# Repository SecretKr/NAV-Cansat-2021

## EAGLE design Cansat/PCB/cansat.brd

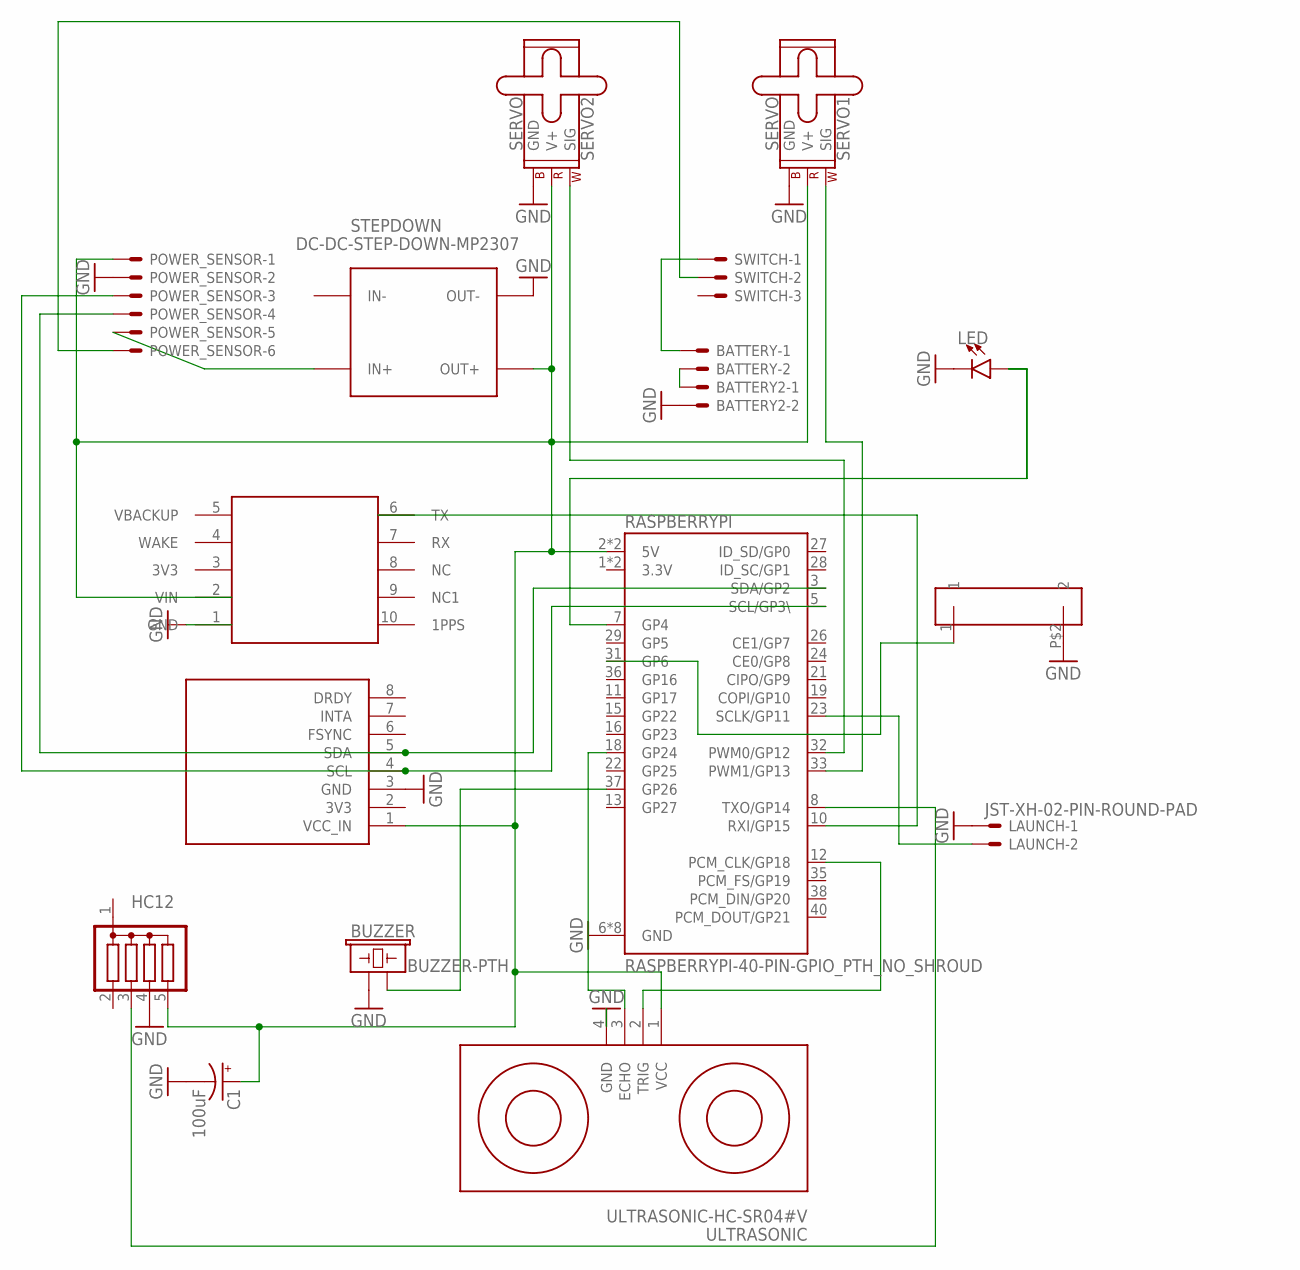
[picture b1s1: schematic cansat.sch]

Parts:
BATTERY, BATTERY2: JST-XH-02-PIN-ROUND-PAD; JST-XH-02-PACKAGE-ROUND-PAD
BUZZER: BUZZER-PTH; BUZZER-12MM
C1: 100uF; CPOL-RADIAL-2.5MM-6.5MM
GPS: AIR530; AIR530FOOTPRINT
HC12: G04R; SIL5
LAUNCH: JST-XH-02-PIN-ROUND-PAD; JST-XH-02-PACKAGE-ROUND-PAD
LED: LED5MM; LED_5MM
MPU: GY-86
POWER_SENSOR: JST-XH-06-PIN-ROUND-PAD; JST-XH-06-PACKAGE-ROUND-PAD
RASPBERRYPI: RASPBERRYPI-40-PIN-GPIO_PTH_NO_SHROUD; 2X20
SENSOR: PENCIL
SERVO1, SERVO2: SERVO; 1X03
STEPDOWN: DC-DC-STEP-DOWN-MP2307
SWITCH: JST-XH-03-PIN-ROUND-PAD; JST-XH-03-PACKAGE-ROUND-PAD
ULTRASONIC: ULTRASONIC-HC-SR04#V

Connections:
3.3V: RASPBERRYPI.1 (3.3V), RASPBERRYPI.17 (3.3V)
GND: BATTERY2.2, BUZZER.+ (1), C1.2 (-), GPS.1 (GND), HC12.4, LAUNCH.1, LED.K (C), MPU.3 (GND), POWER_SENSOR.2, RASPBERRYPI.6 (GND), RASPBERRYPI.9 (GND), RASPBERRYPI.14 (GND), RASPBERRYPI.20 (GND), RASPBERRYPI.25 (GND), RASPBERRYPI.30 (GND), RASPBERRYPI.34 (GND), RASPBERRYPI.39 (GND), SENSOR.P$2 (2), SERVO1.3 (GND), SERVO2.3 (GND), STEPDOWN.OUT-, ULTRASONIC.4 (GND)
unnamed: C1.1 (+), GPS.2 (VIN), HC12.5, MPU.1 (VCC_IN), POWER_SENSOR.1, RASPBERRYPI.2 (5V), RASPBERRYPI.4 (5V), SERVO1.2 (V+), SERVO2.2 (V+), STEPDOWN.OUT+, ULTRASONIC.1 (VCC)
unnamed: LED.A, RASPBERRYPI.7 (GP4)
unnamed: BATTERY.2, BATTERY2.1
unnamed: BATTERY.1, SWITCH.1
unnamed: POWER_SENSOR.6, SWITCH.2
unnamed: GPS.6 (TX), RASPBERRYPI.10 (RXI/GP15)
unnamed: HC12.3, RASPBERRYPI.8 (TXO/GP14)
unnamed: MPU.5 (SDA), POWER_SENSOR.4, RASPBERRYPI.3 (SDA/GP2)
unnamed: MPU.4 (SCL), POWER_SENSOR.3, RASPBERRYPI.5 (SCL/GP3\)
unnamed: RASPBERRYPI.12 (PCM_CLK/GP18), ULTRASONIC.2 (TRIG)
unnamed: RASPBERRYPI.18 (GP24), ULTRASONIC.3 (ECHO)
unnamed: RASPBERRYPI.32 (PWM0/GP12), SERVO2.1 (SIG)
unnamed: RASPBERRYPI.33 (PWM1/GP13), SERVO1.1 (SIG)
unnamed: BUZZER.- (2), RASPBERRYPI.37 (GP26)
unnamed: LAUNCH.2, RASPBERRYPI.23 (SCLK/GP11)
unnamed: POWER_SENSOR.5, STEPDOWN.IN+
unnamed: RASPBERRYPI.31 (GP6), SENSOR.1

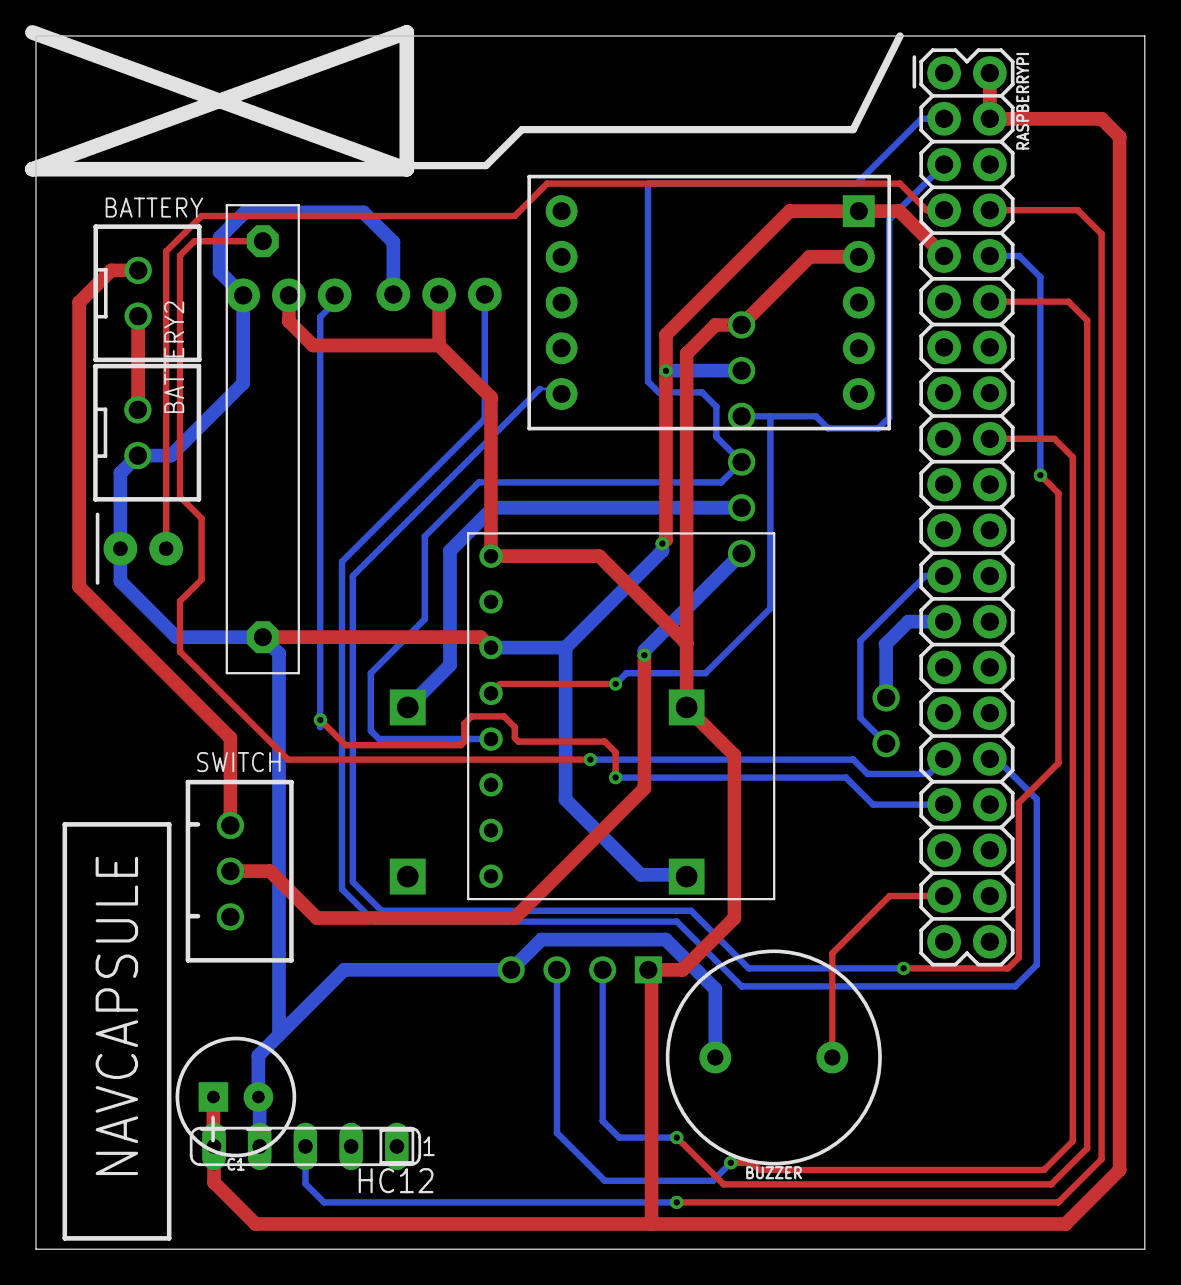
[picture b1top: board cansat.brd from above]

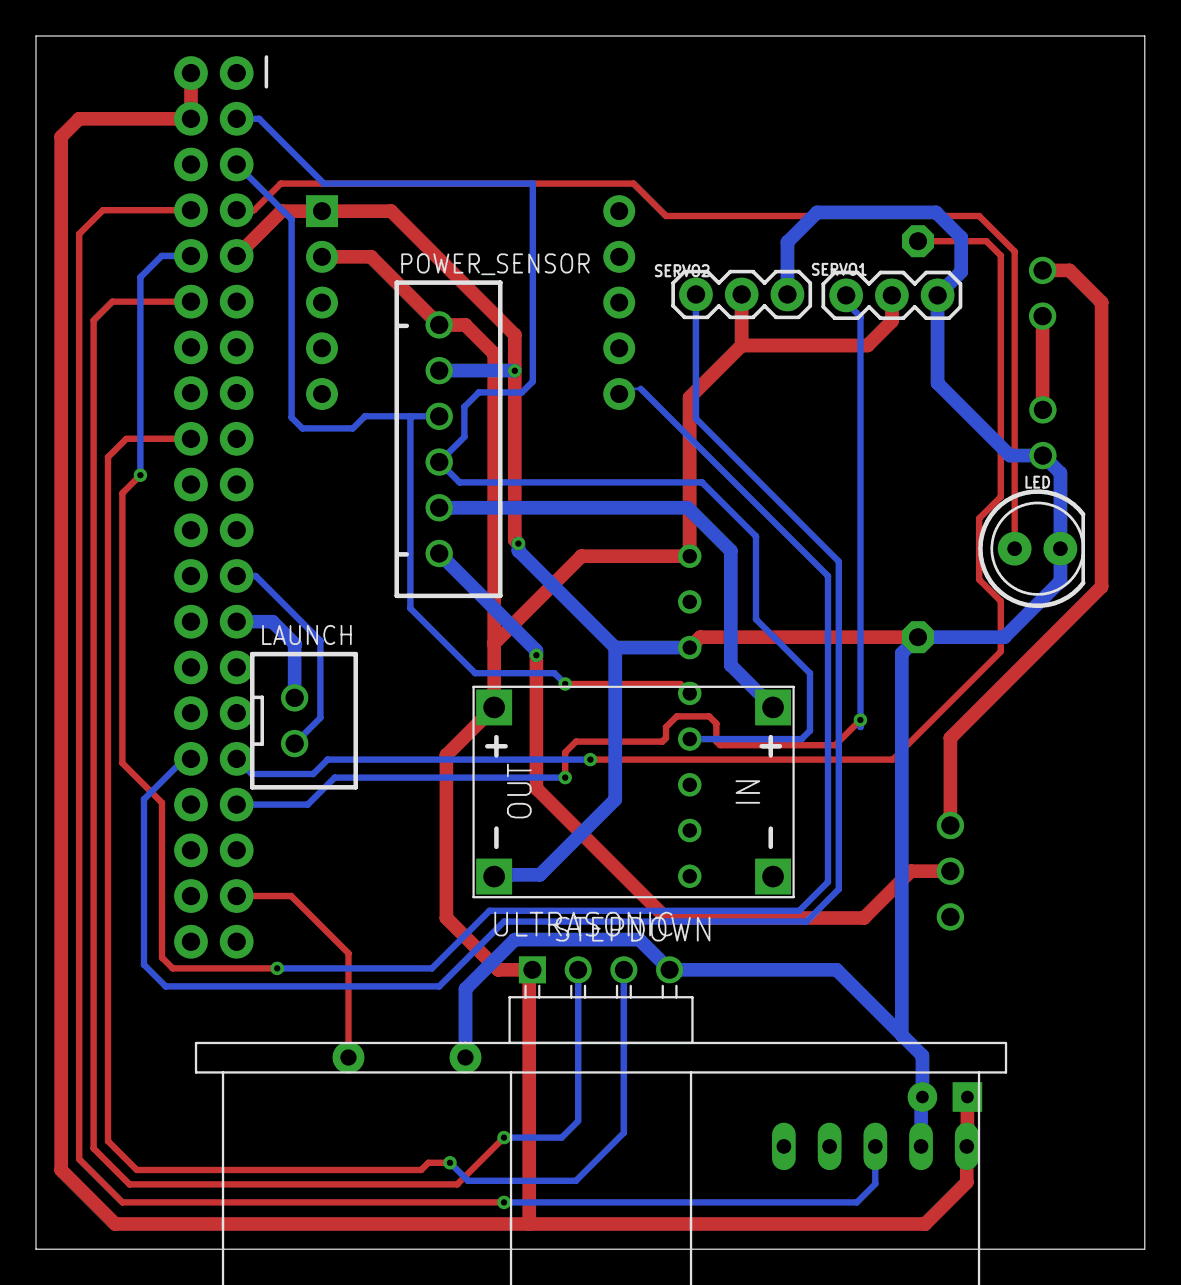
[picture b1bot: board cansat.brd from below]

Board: 2 copper layers, 61.6 x 67.4 mm, 17 parts (7 on the bottom side), 19 nets.

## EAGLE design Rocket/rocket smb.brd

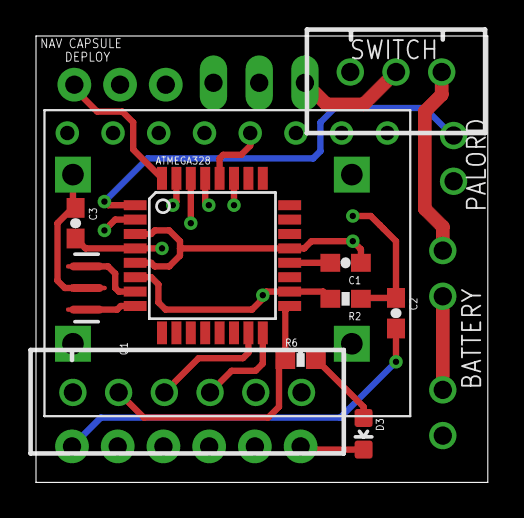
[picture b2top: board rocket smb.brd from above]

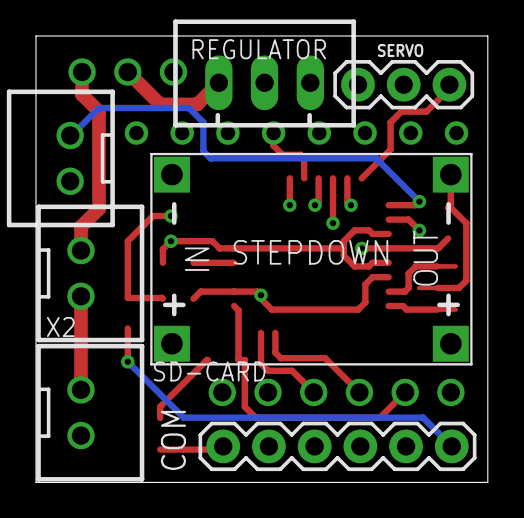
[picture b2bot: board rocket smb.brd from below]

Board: 4 copper layers, 25.1 x 24.8 mm, 18 parts (7 on the bottom side), 21 nets.

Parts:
ATMEGA328: ATMEGA328; TQFP32-08
BATTERY: JST-XH-02-PIN-ROUND-PAD; JST-XH-02-PACKAGE-ROUND-PAD
C1, C2, C3: 0.1uF; 0603-CAP
COM: FTDI Basic; 1X06
D3: Green; 0603-LED-ALT1
MPU: GY-86
PALORD: JST-XH-02-PIN-ROUND-PAD; JST-XH-02-PACKAGE-ROUND-PAD
Q1: 8/16/20MHz; RESONATOR-SMD-1:1
R2: 10K; 0603-RES
R6: 330; 0603-RES
REGULATOR: JST-XH-03-PIN-LONG-PAD; JST-XH-03-PACKAGE-LONG-PAD
SD-CARD: JST-XH-06-PIN-ROUND-PAD; JST-XH-06-PACKAGE-ROUND-PAD
SERVO: SERVO; 1X03
STEPDOWN: DC-DC-STEP-DOWN-MP2307
SWITCH: JST-XH-03-PIN-ROUND-PAD; JST-XH-03-PACKAGE-ROUND-PAD
X2: JST-XH-02-PIN-ROUND-PAD; JST-XH-02-PACKAGE-ROUND-PAD

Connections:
AREF: ATMEGA328.20, C1.2
D2: ATMEGA328.32, SERVO.1
D3: ATMEGA328.1, PALORD.2
D4: ATMEGA328.2, SD-CARD.6
DTR: C2.2, COM.1
GND: ATMEGA328.3, ATMEGA328.5, ATMEGA328.21, C1.1, C3.1, COM.5, COM.6, D3.C, MPU.3, PALORD.1, Q1.2, REGULATOR.2, SD-CARD.1, SERVO.3, STEPDOWN.OUT-, X2.2
MISO: ATMEGA328.16, SD-CARD.3
MOSI: ATMEGA328.15, SD-CARD.4
unnamed: BATTERY.2, X2.1
unnamed: BATTERY.1, SWITCH.1
unnamed: REGULATOR.1, STEPDOWN.IN+, SWITCH.2
unnamed: ATMEGA328.28, MPU.4
unnamed: ATMEGA328.27, MPU.5
unnamed: D3.A, R6.2
unnamed: ATMEGA328.8, Q1.3
unnamed: ATMEGA328.7, Q1.1
RESET: ATMEGA328.29, C2.1, R2.1
RXI: ATMEGA328.30, COM.3
SCK: ATMEGA328.17, R6.1, SD-CARD.5
TXO: ATMEGA328.31, COM.2
VCC: ATMEGA328.4, ATMEGA328.6, ATMEGA328.18, C3.2, COM.4, MPU.1, R2.2, REGULATOR.3, SD-CARD.2, SERVO.2, STEPDOWN.OUT+

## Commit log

2022-01-02 finished
2023-01-25 second commit

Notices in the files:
parts and their libraries:
SparkFun-Connectors: Licensing: Creative Commons ShareAlike 4.0 International - https://creativecommons.org/licenses/by-sa/4.0
diy-modules: Released under the Creative Commons Attribution 4.0 International License: http://creativecommons.org/licenses/by/4.0
